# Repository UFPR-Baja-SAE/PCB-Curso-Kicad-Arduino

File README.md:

# PCB-Curso-Kicad-Arduino
PCB do curso de KiCad da SEATEL 2023
Design de uma PCB utilizando o ATmega328P-PU para fazer um arduino simples. 
Este projeto foi utilizado como conteudo complementar para o curso de KiCad da Equipe UFPR BAJA SAE, o projeto de schematic e pcb são inspirados e baseados no projeto de João Alves, especificamente o CSEduino V4. Link para a fonte https://jpralves.net/pages/cseduinoworld.html

Em adendo para os alunos do curso, uma breve instrução a como usar labels globais.

1. Na barra de ferramentas, selecione a opção "Place Global Label" (ou uma opção semelhante, dependendo da versão).
2. Clique no local do esquemático onde deseja adicionar a label global.
3. Uma janela de diálogo será exibida, onde você pode inserir o nome da label global.
4. Digite o nome desejado para a label global e pressione "Enter" ou clique em "OK" para confirmar.
5. A label global será adicionada ao esquemático e você pode movê-la para a posição desejada, se necessário.

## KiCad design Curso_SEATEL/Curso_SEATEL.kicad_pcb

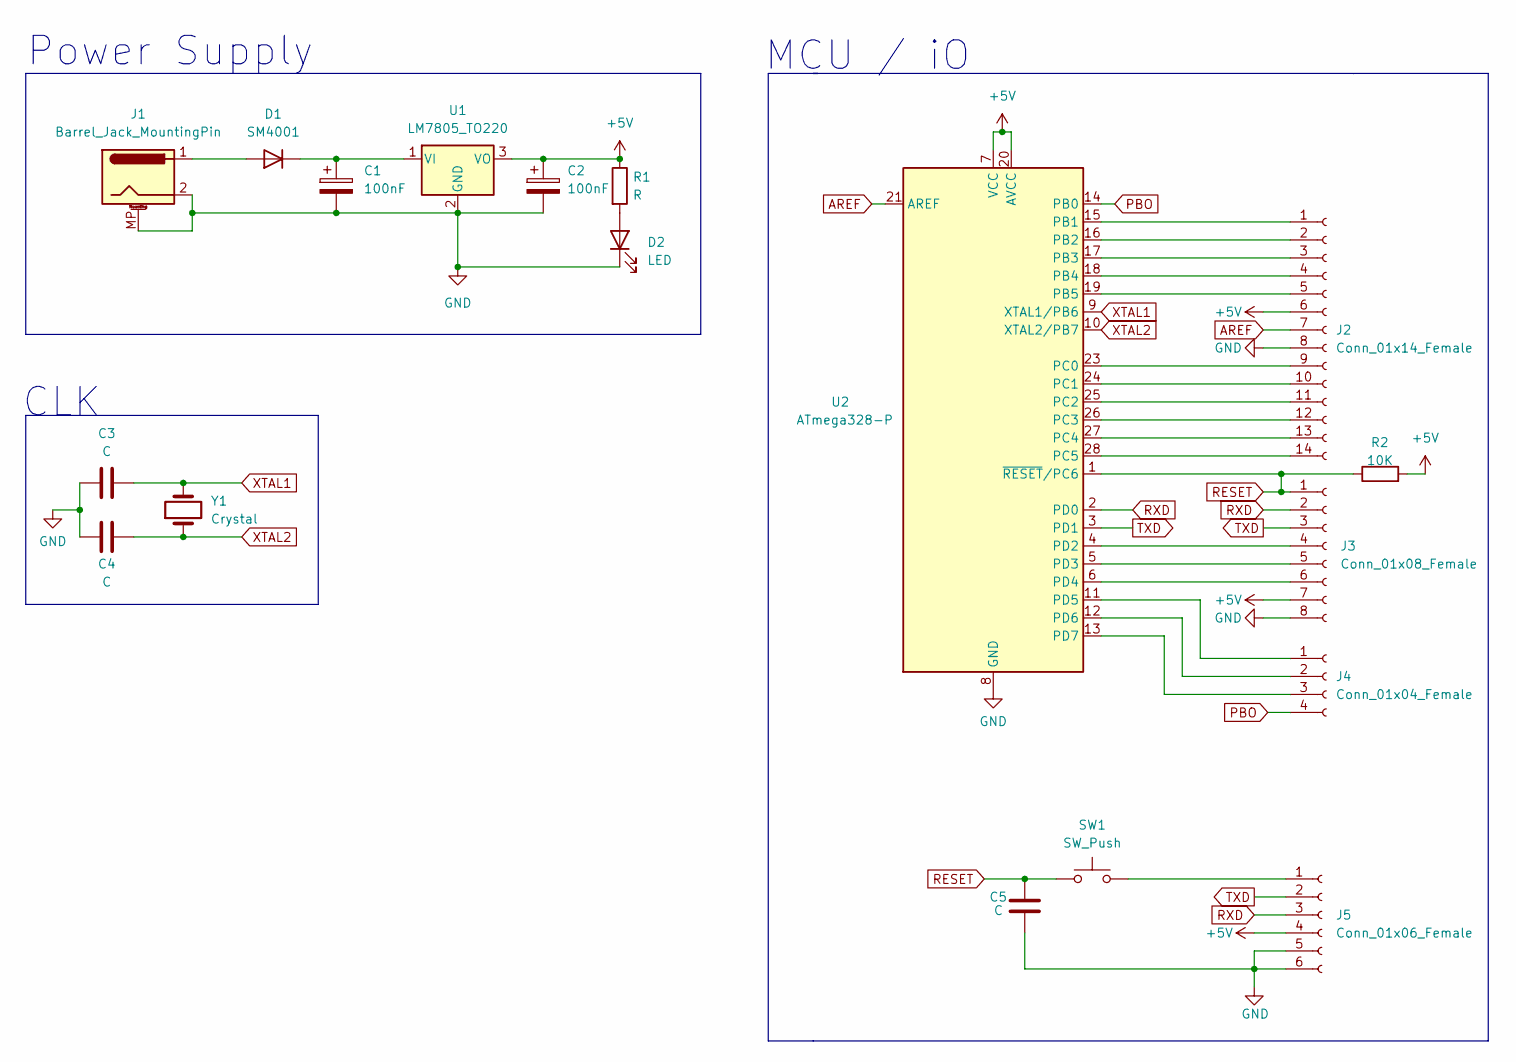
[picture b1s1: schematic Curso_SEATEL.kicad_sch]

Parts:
C1, C2: 100nF; CP_Radial_D6.3mm_P2.50mm
C3, C4, C5: C; C_0603_1608Metric
D1: SM4001; D_MELF
D2: LED; LED_0603_1608Metric
J1: Barrel_Jack_MountingPin; BarrelJack_GCT_DCJ200-10-A_Horizontal
J2: Conn_01x14_Female; PinSocket_1x14_P2.54mm_Vertical
J3: Conn_01x08_Female; PinSocket_1x08_P2.54mm_Vertical
J4: Conn_01x04_Female; PinSocket_1x04_P2.54mm_Vertical
J5: Conn_01x06_Female; PinSocket_1x06_P1.27mm_Vertical
R1: R; R_0603_1608Metric
R2: 10K; R_0603_1608Metric
SW1: SW_Push; SW_DIP_SPSTx01_Slide_6.7x4.1mm_W6.73mm_P2.54mm_LowProfile_J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
U1: LM7805_TO220; TO-220-3_Vertical
U2: ATmega328-P; DIP-28_W7.62mm
Y1: Crystal; Crystal_HC52-8mm_Vertical

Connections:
+5V: C2.1, J2.6, J3.7, J5.4, R1.1, R2.2, U1.3 (VO), U2.7 (VCC), U2.20 (AVCC)
AREF: J2.7, U2.21 (AREF)
GND: C1.2, C2.2, C3.1, C4.2, C5.1, D2.1 (K), J1.2, J1.MP (MountPin), J2.8, J3.8, J5.5, J5.6, U1.2 (GND), U2.8 (GND), U2.22 (GND)
unnamed: C1.1, D1.1 (K), U1.1 (VI)
unnamed: D1.2 (A), J1.1
unnamed: D2.2 (A), R1.2
unnamed: J2.1, U2.15 (PB1)
unnamed: J2.2, U2.16 (PB2)
unnamed: J2.3, U2.17 (PB3)
unnamed: J2.4, U2.18 (PB4)
unnamed: J2.5, U2.19 (PB5)
unnamed: J2.9, U2.23 (PC0)
unnamed: J2.10, U2.24 (PC1)
unnamed: J2.11, U2.25 (PC2)
unnamed: J2.12, U2.26 (PC3)
unnamed: J2.13, U2.27 (PC4)
unnamed: J2.14, U2.28 (PC5)
unnamed: J3.4, U2.4 (PD2)
unnamed: J3.5, U2.5 (PD3)
unnamed: J3.6, U2.6 (PD4)
unnamed: J4.1, U2.11 (PD5)
unnamed: J4.2, U2.12 (PD6)
unnamed: J4.3, U2.13 (PD7)
unnamed: J5.1, SW1.2
PBO: J4.4, U2.14 (PB0)
RESET: C5.2, J3.1, R2.1, SW1.1, U2.1 (~RESET/PC6)
RXD: J3.2, J5.3, U2.2 (PD0)
TXD: J3.3, J5.2, U2.3 (PD1)
XTAL1: C3.2, U2.9 (XTAL1/PB6), Y1.2
XTAL2: C4.1, U2.10 (XTAL2/PB7), Y1.1

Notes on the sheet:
MCU / iO
Power Supply
CLK

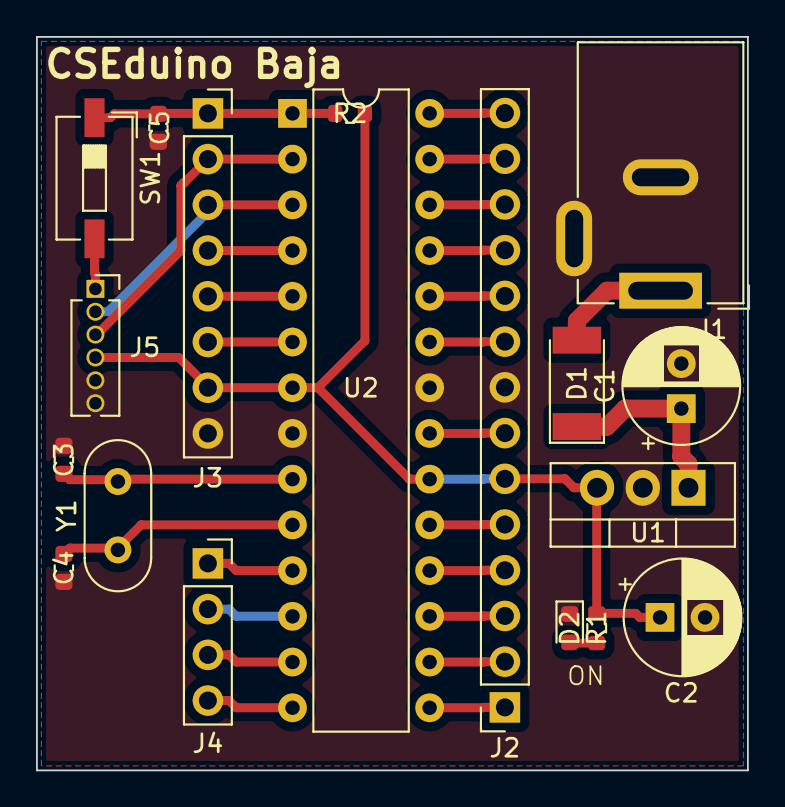
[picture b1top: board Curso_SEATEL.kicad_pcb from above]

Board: 2 copper layers, 39.5 x 40.8 mm, 18 parts (0 on the bottom side), 30 nets.

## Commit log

2023-05-20 PCB-Arduino
2023-05-21 Create README.md
    adicionado o readme para deixar o projeto publico
